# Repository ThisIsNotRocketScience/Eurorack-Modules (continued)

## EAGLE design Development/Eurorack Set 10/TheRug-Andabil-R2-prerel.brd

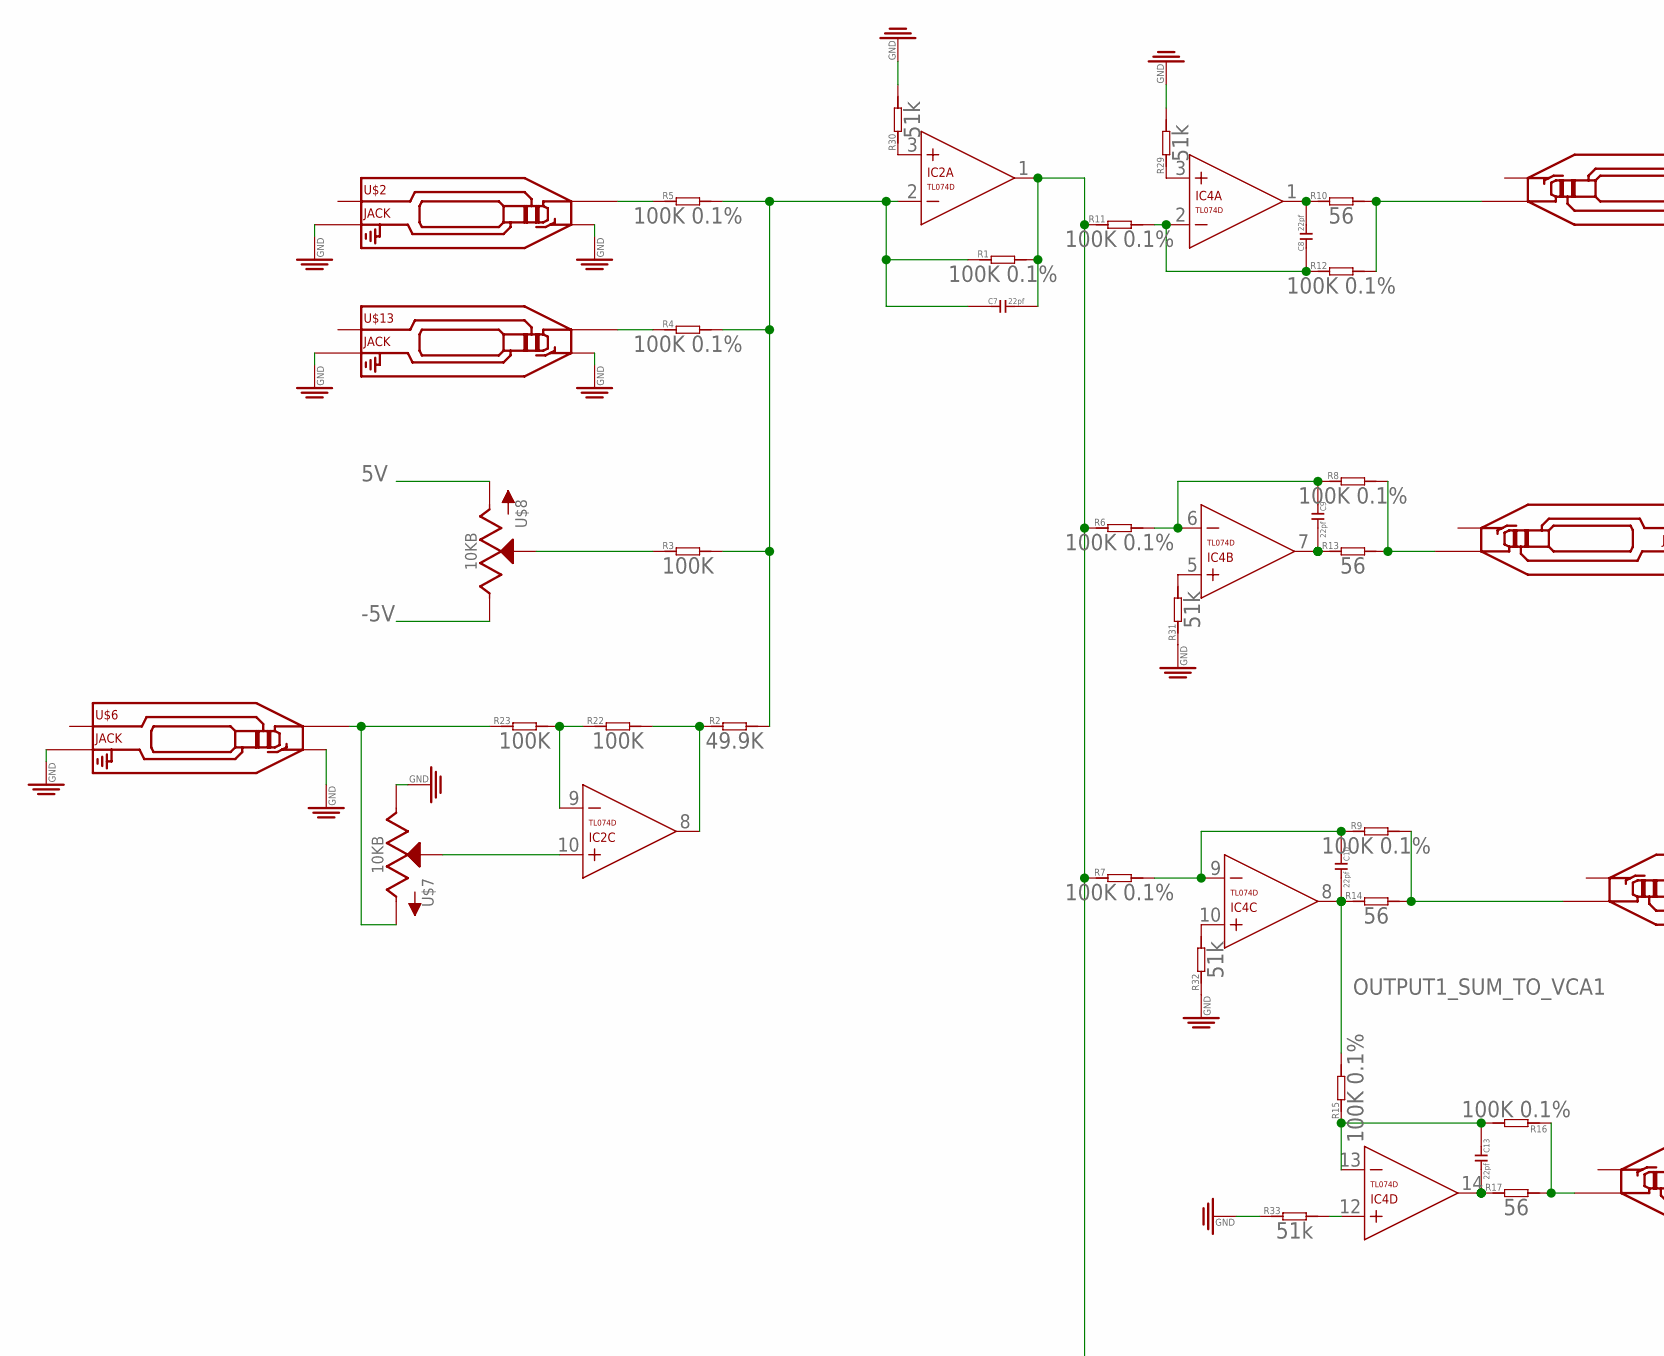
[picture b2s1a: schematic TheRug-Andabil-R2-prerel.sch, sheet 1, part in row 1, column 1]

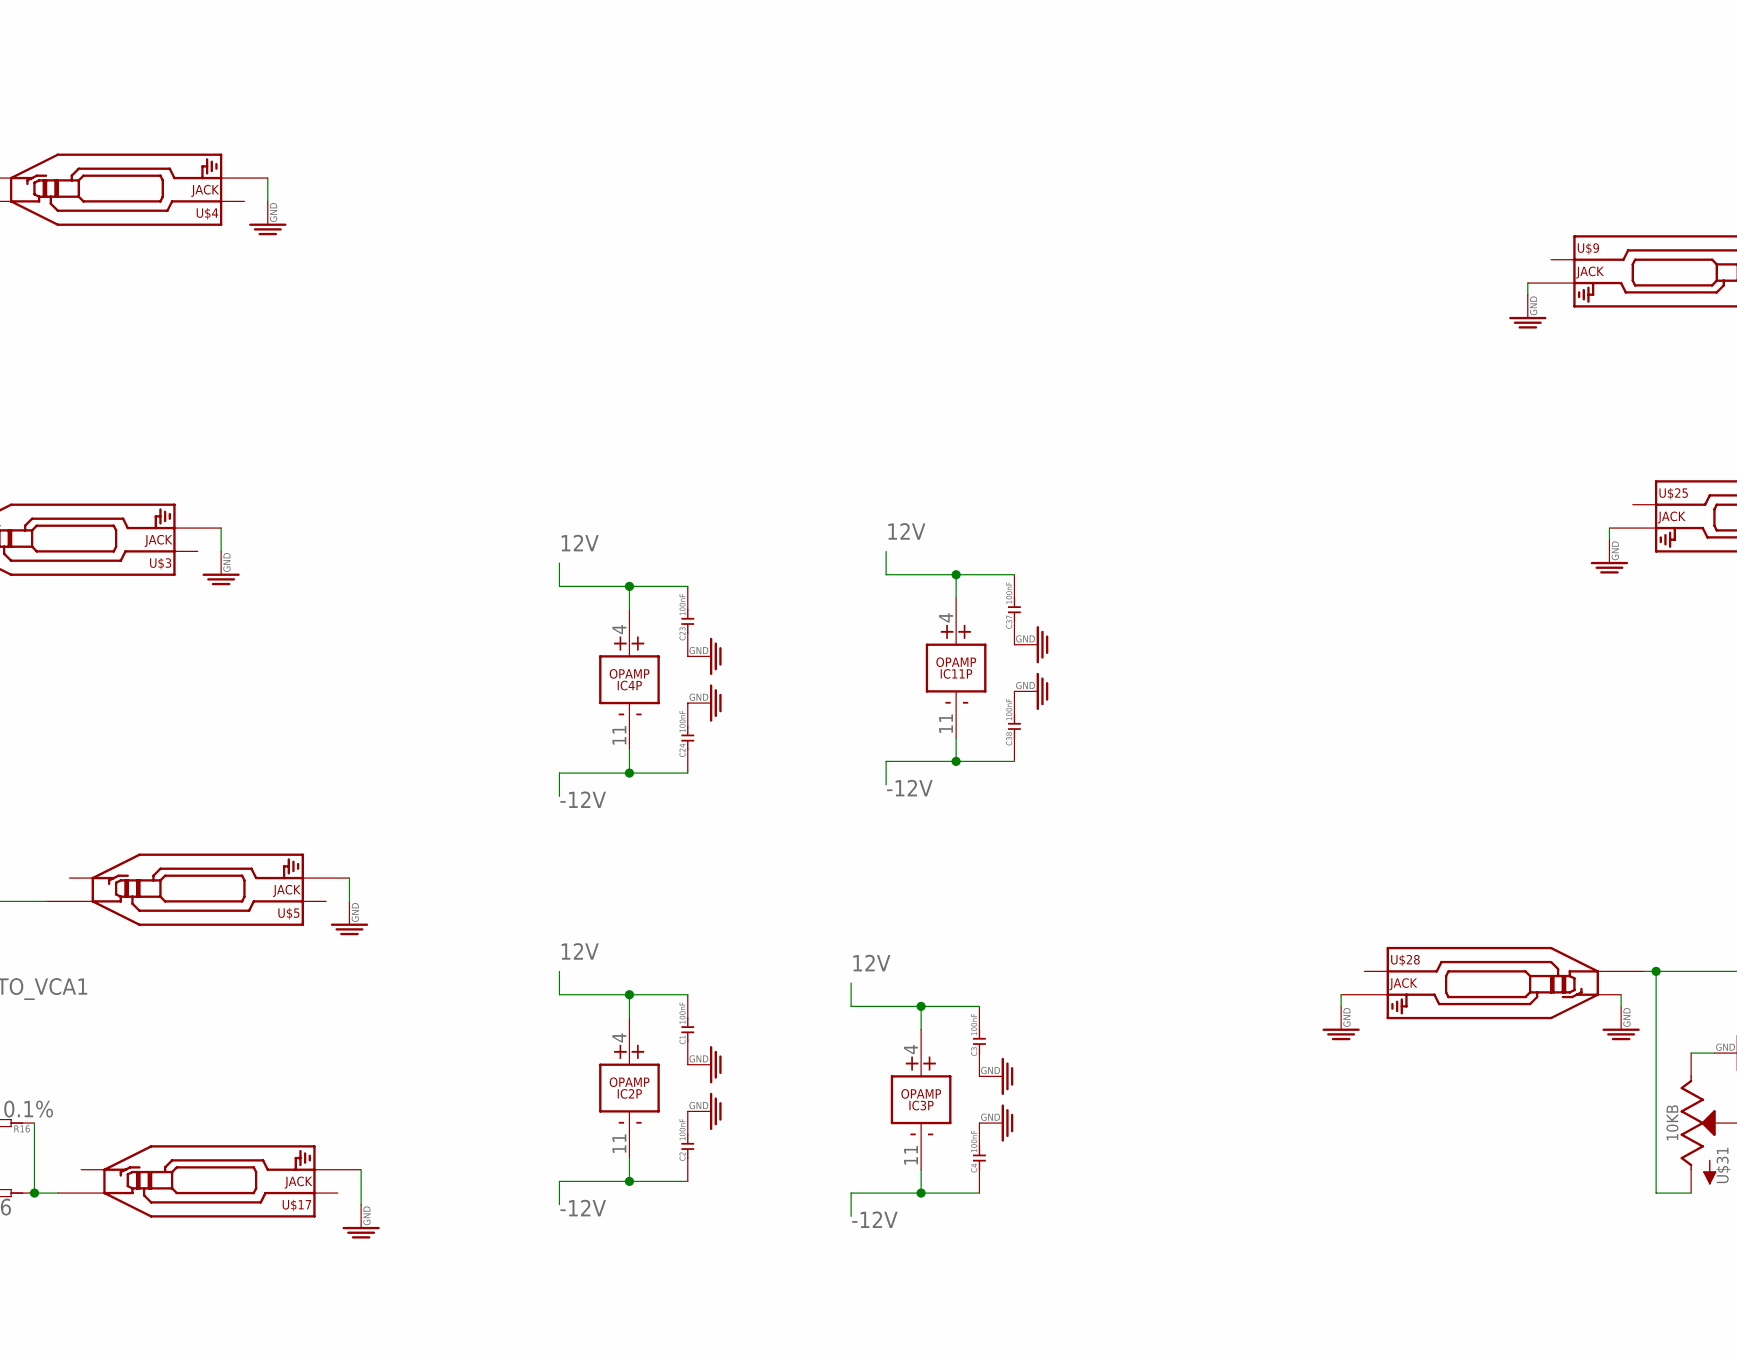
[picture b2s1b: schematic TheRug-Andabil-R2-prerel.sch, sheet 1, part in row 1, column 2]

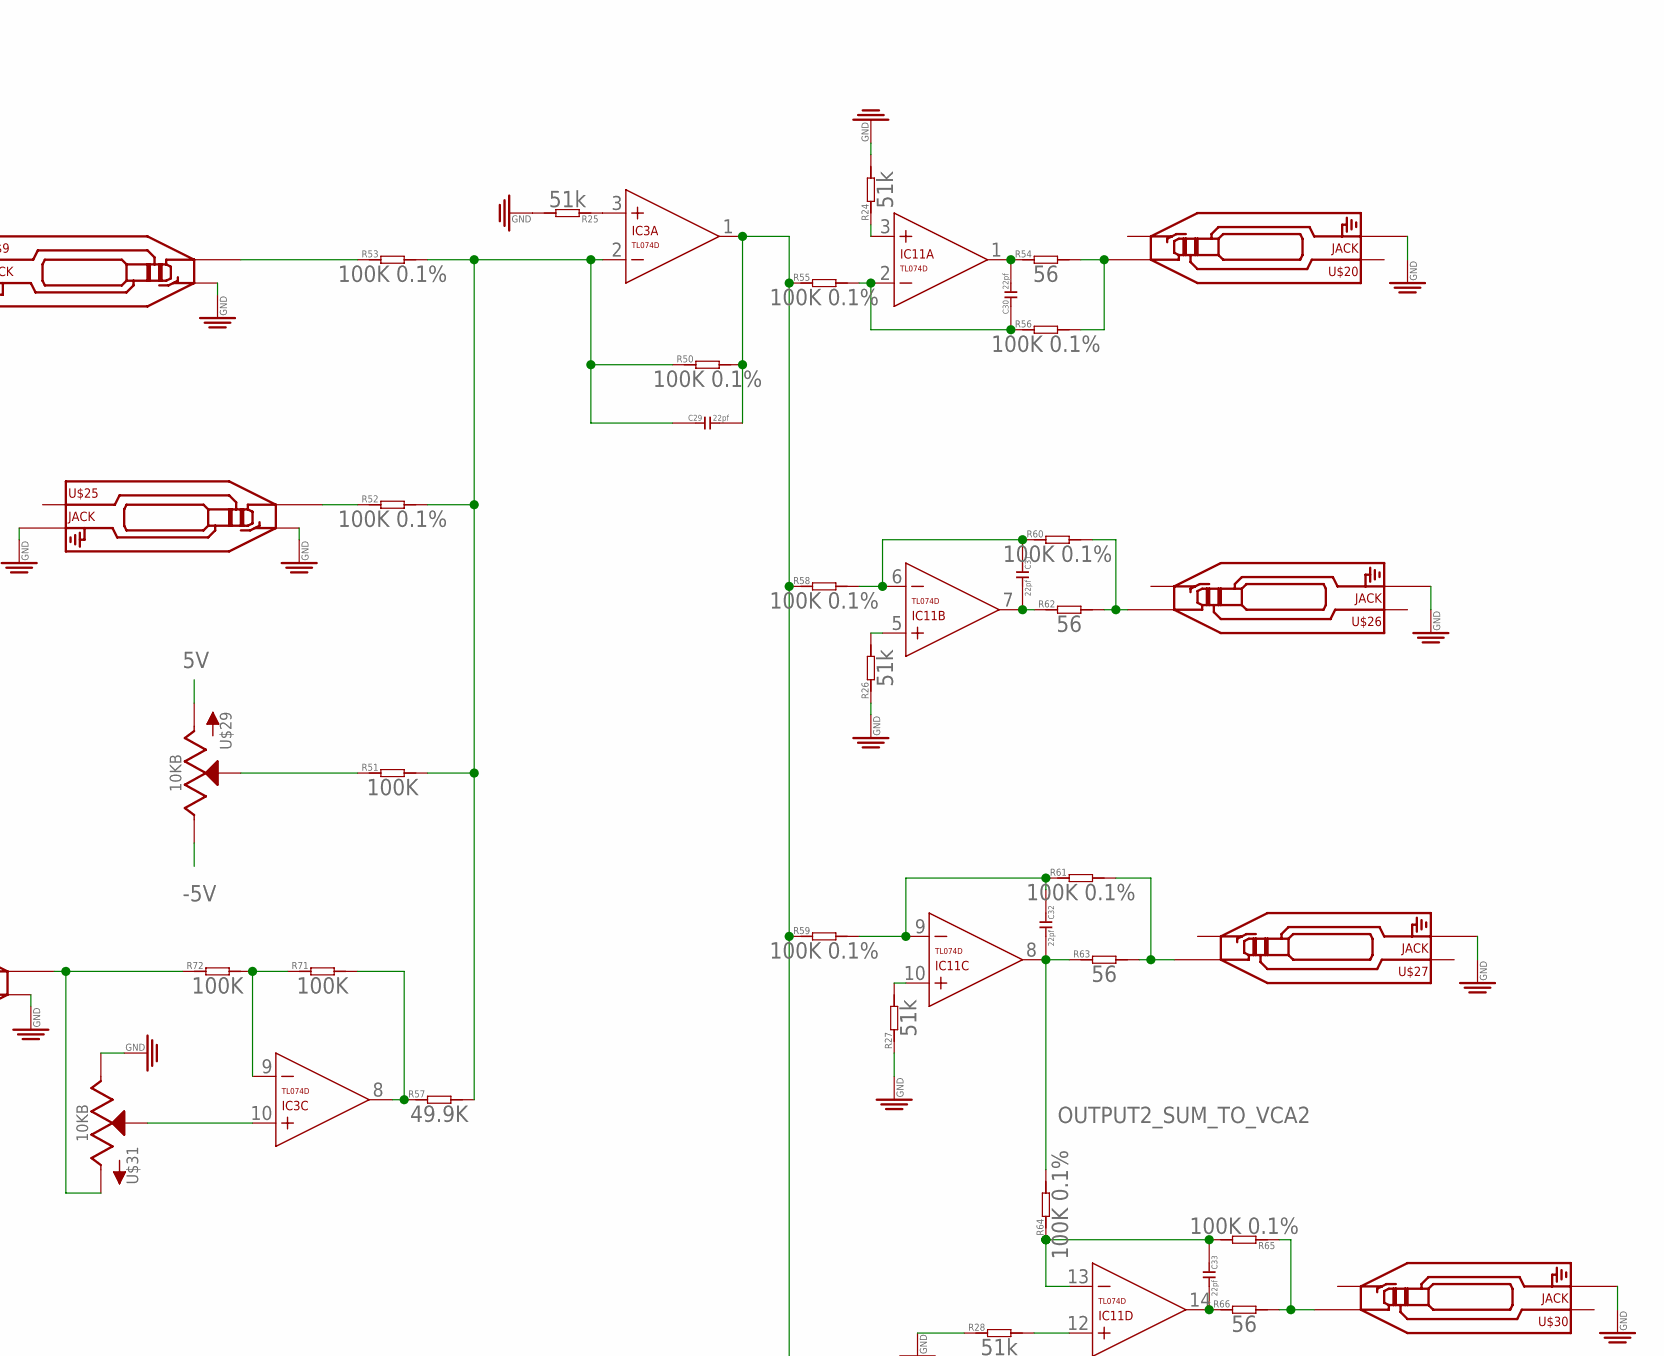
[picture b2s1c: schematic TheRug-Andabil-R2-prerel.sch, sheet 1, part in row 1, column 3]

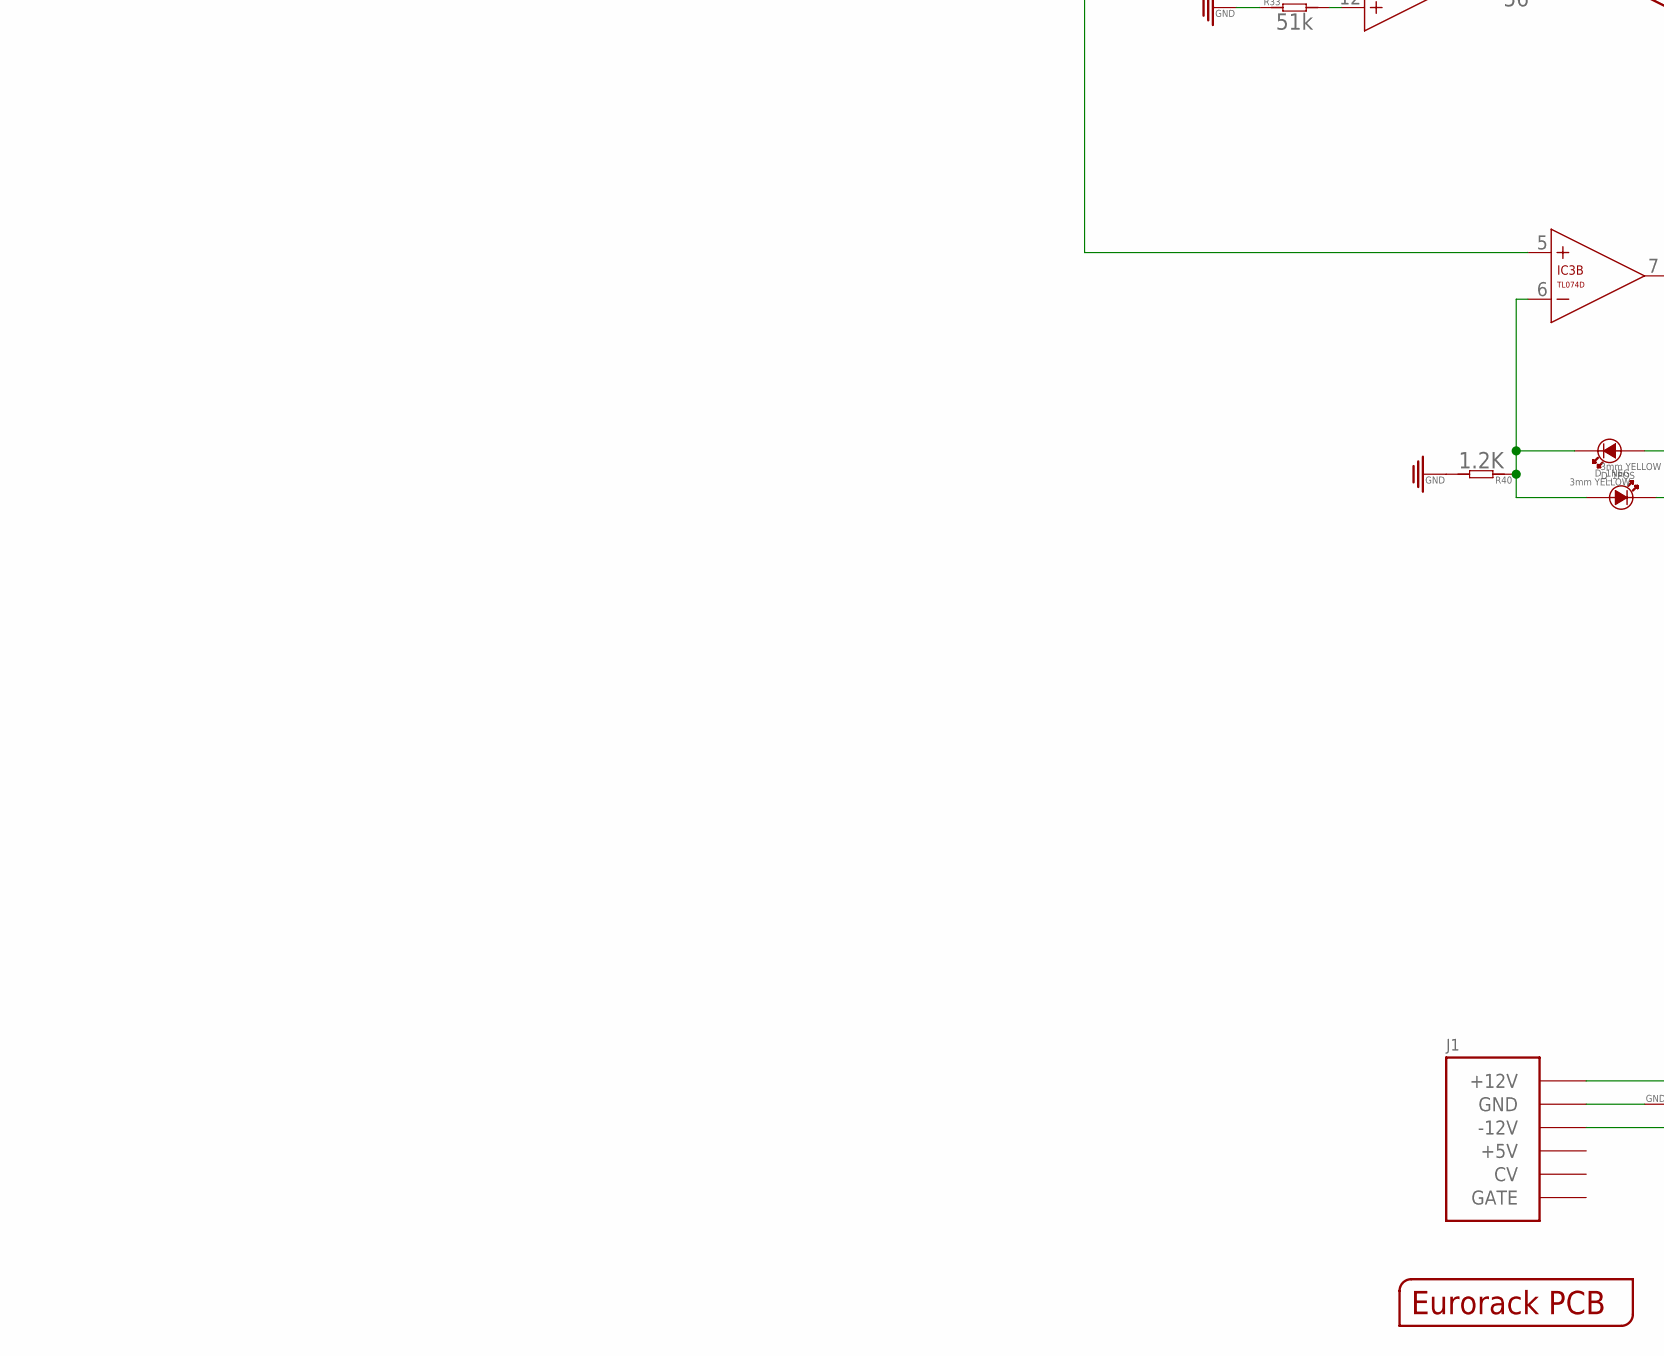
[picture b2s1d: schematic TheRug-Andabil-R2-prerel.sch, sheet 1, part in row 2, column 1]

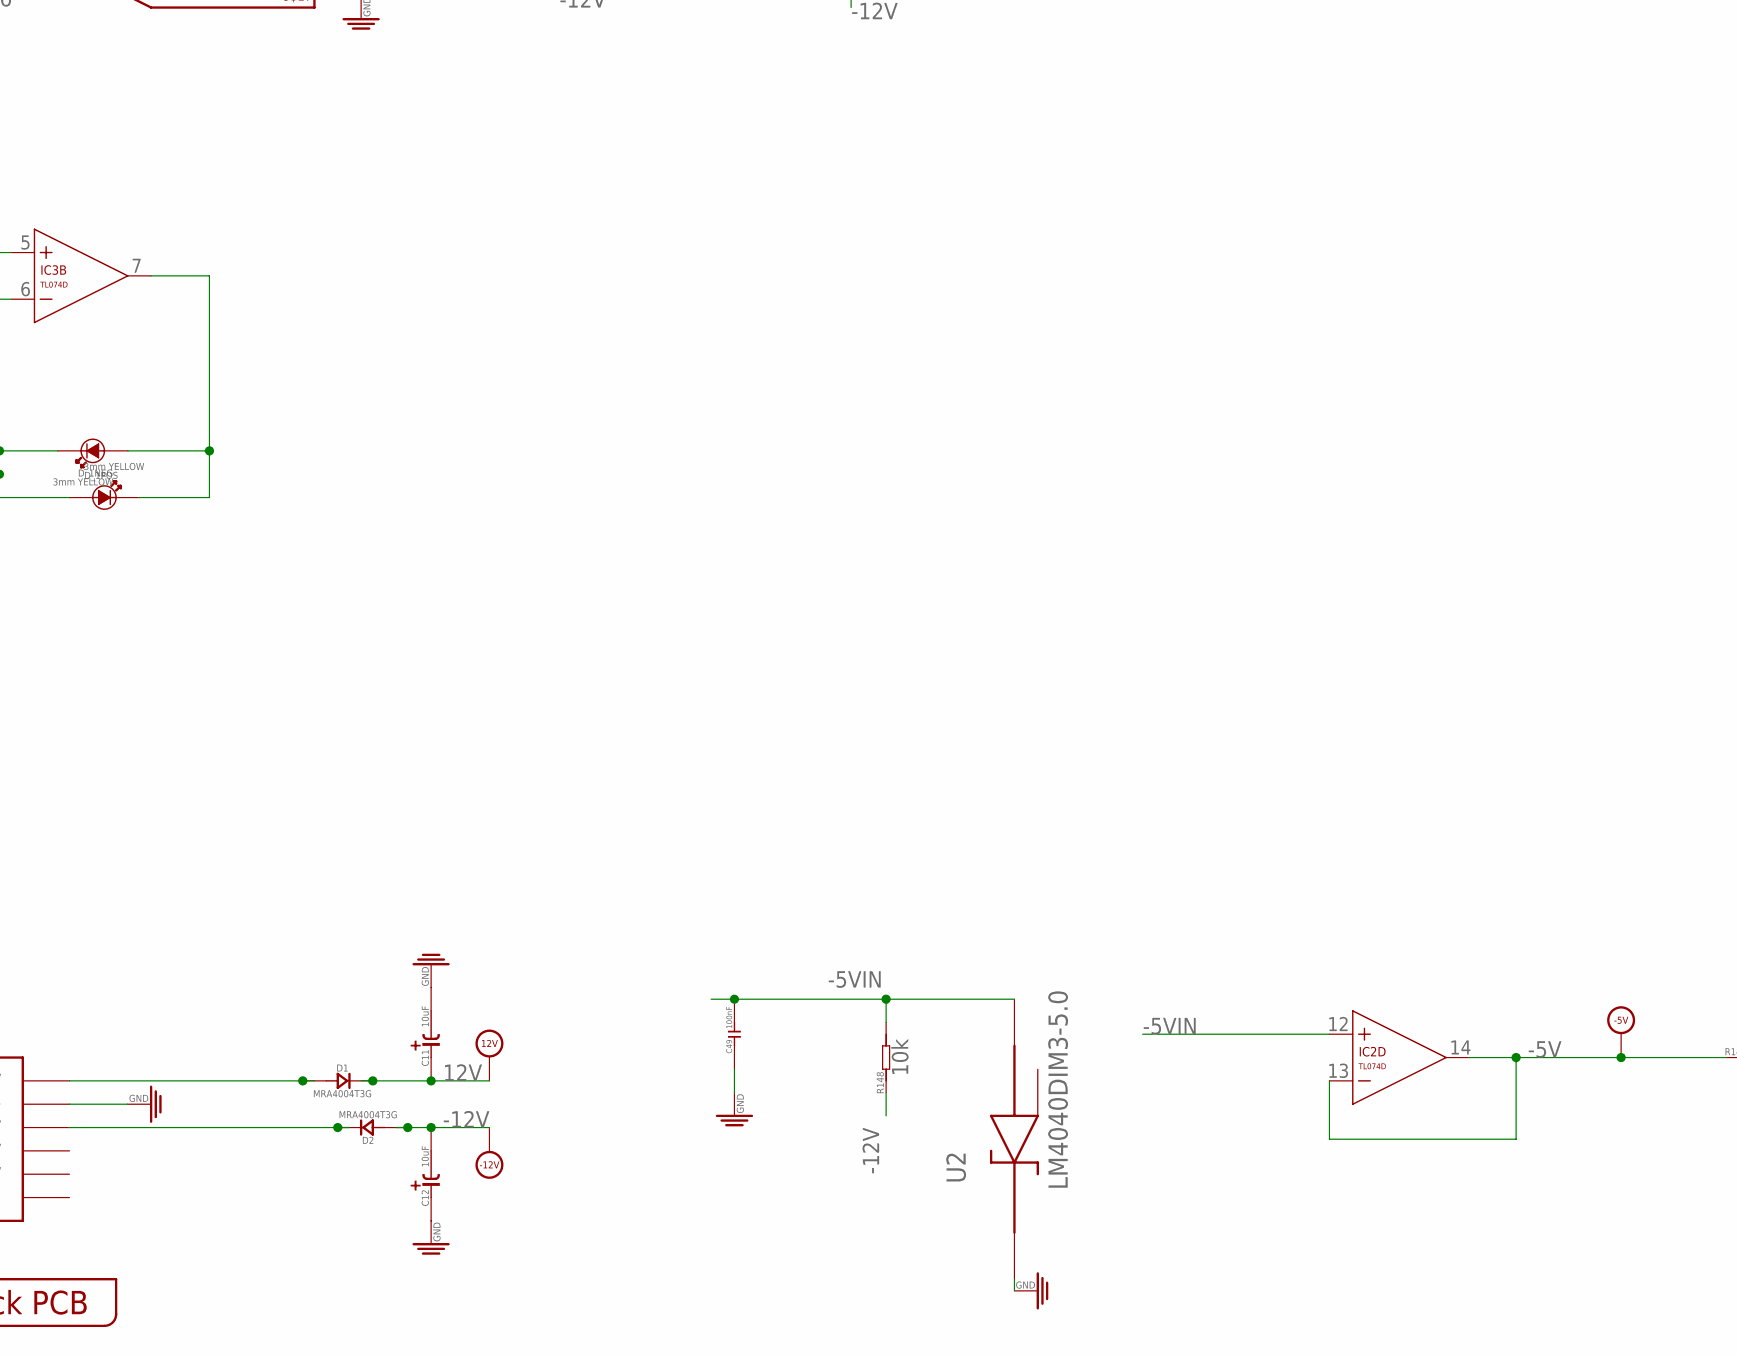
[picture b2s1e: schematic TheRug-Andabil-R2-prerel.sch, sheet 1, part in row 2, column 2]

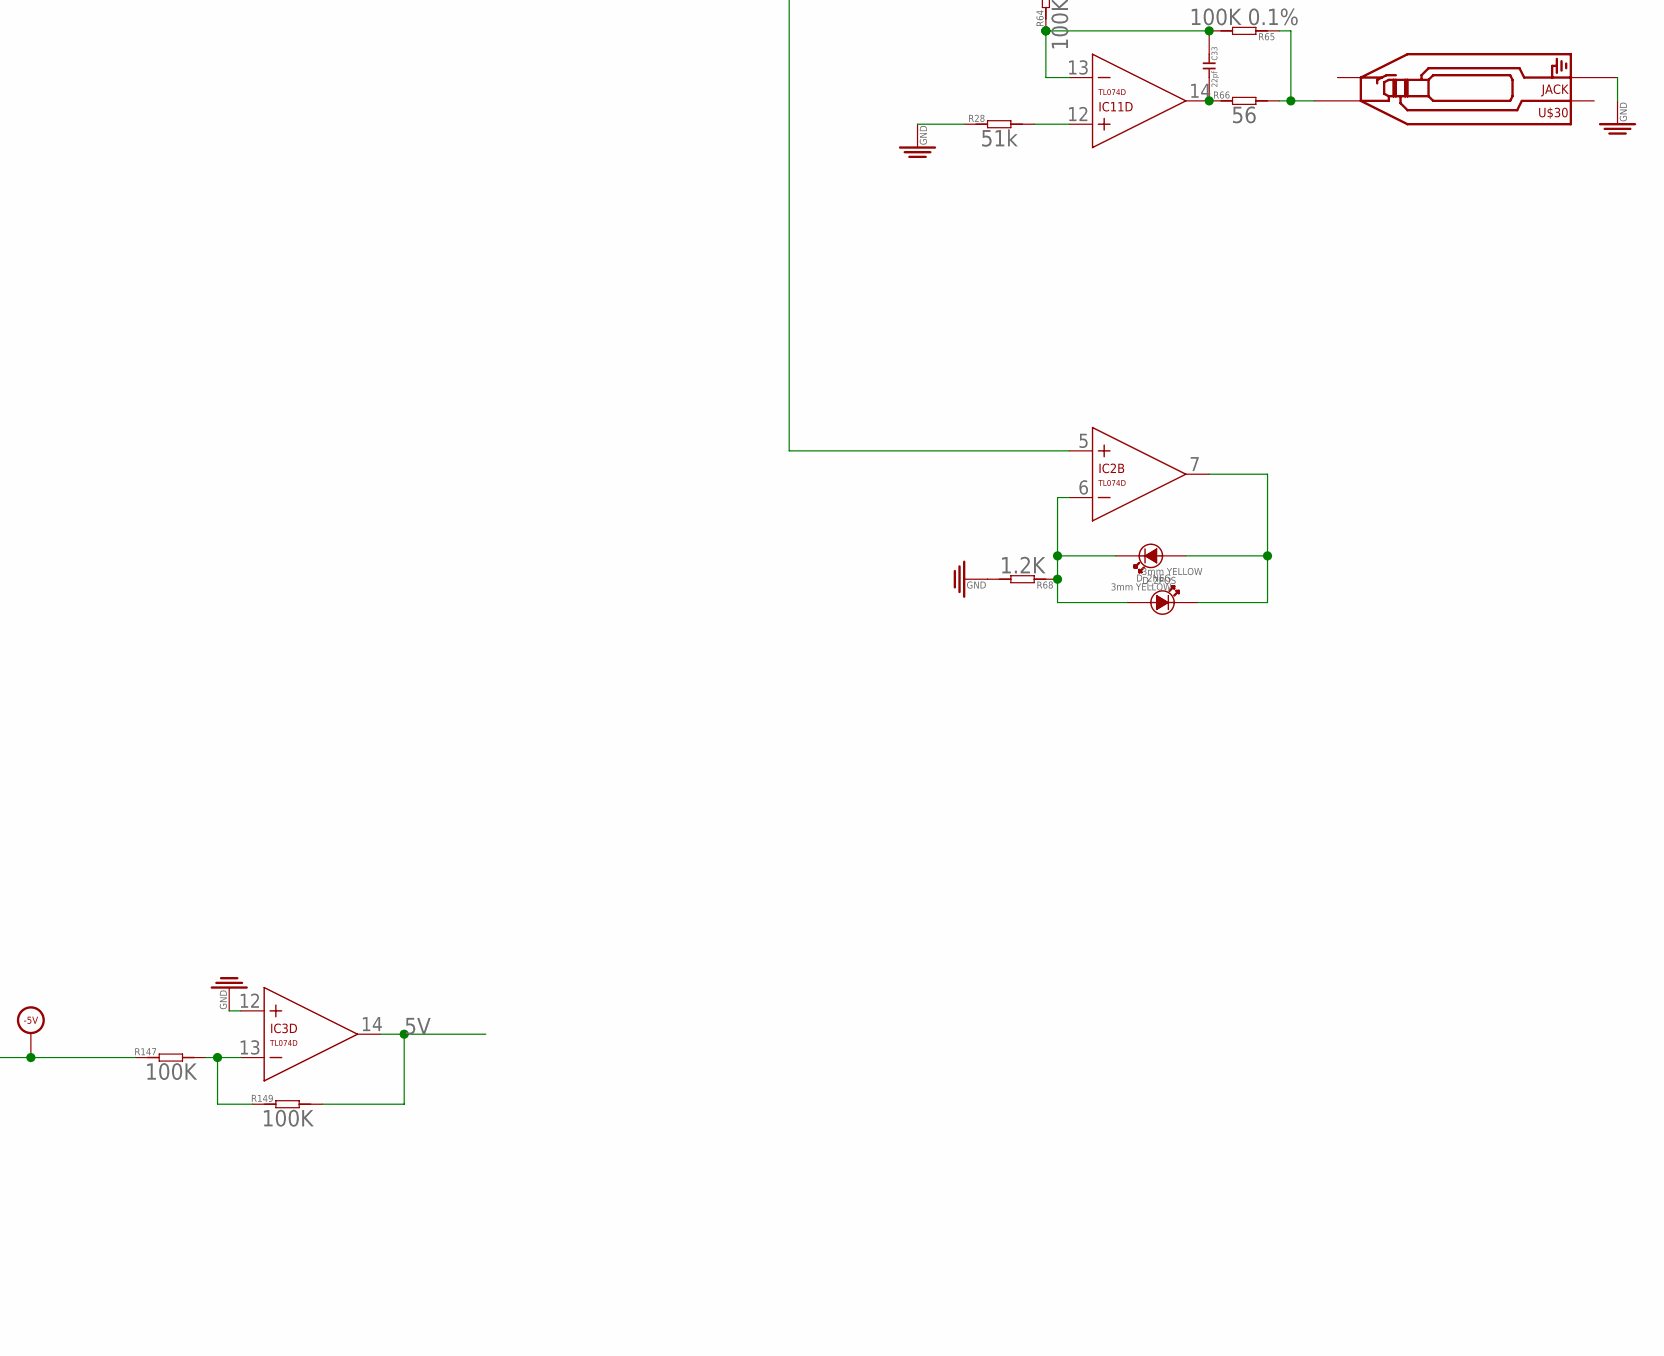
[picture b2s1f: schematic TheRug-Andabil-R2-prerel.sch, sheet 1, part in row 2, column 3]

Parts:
C1, C2, C3, C4, C23, C24, C37, C38: 100nF; C0603
C7, C8, C9, C10, C13, C29, C30, C31, C32, C33: 22pf; C0603
C11, C12: 10uF; CASE-A_3216
C49: 100nF; C0603; MPN 06035C104KAT2A
D1, D2: MRA4004T3G; DO-214AC; MPN US1G-E3/5AT
D_1NEG, D_1POS, D_2NEG, D_2POS: 3mm YELLOW; 3MMLED
IC2, IC3, IC4, IC11: TL074D; SO14
J1: POWERSHROUDED; POWER_16_SHROUDED
R1, R4, R5, R6, R7, R8, R9, R11, R12, R15, R16, R50, R52, R53, R55, R56, R58, R59, R60, R61, R64, R65: 100K 0.1%; R0603
R2, R57: 49.9K; R0603
R3, R22, R23, R51, R71, R72, R147, R149: 100K; R0603
R10, R13, R14, R17, R54, R62, R63, R66: 56; R0603
R24, R25, R26, R27, R28, R29, R30, R31, R32, R33: 51k; R0603
R40, R68: 1.2K; R0603
R148: 10k; R0603
U2: LM4040DIM3-5.0; SOT95P237X112-3N
U$1: EURORACK_PCB12HP; EURORACK12HPPCB
U$2, U$3, U$4, U$5, U$6, U$9, U$13, U$17, U$20, U$25, U$26, U$27, U$28, U$30: JACK; 3.5MM-JACK-SWITCH-13MM-NOHOLES
U$7, U$8, U$29, U$31: 10KB; ALPS_POT_SQUAREHOLES

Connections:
5V: IC3.14 (OUT), R149.2, U$8.P$3 (A), U$29.P$3 (A)
12V: C1.2, C3.2, C11.+ (1), C23.2, C37.2, D1.2 (-), IC2.4 (V+), IC3.4 (V+), IC4.4 (V+), IC11.4 (V+); also elsewhere on the board
-5V: IC2.13 (-IN), IC2.14 (OUT), R147.1, U$8.P$1 (E), U$29.P$1 (E); also elsewhere on the board
-5VIN: C49.2, IC2.12 (+IN), R148.2, U2.2 (ANODE)
-5V_TO_5V: IC3.13 (-IN), R147.2, R149.1
-12V: C2.1, C4.1, C12.- (2), C24.1, C38.1, D2.1 (+), IC2.11 (V-), IC3.11 (V-), IC4.11 (V-), IC11.11 (V-), R148.1; also elsewhere on the board
GND: C1.1, C2.2, C3.1, C4.2, C11.- (2), C12.+ (1), C23.1, C24.2, C37.1, C38.2, C49.1, IC3.12 (+IN), J1.3 (GND), J1.4 (GND), J1.5 (GND), J1.6 (GND), J1.7 (GND), J1.8 (GND), R24.2, R25.2, R26.1, R27.1, R28.1, R29.2, R30.2, R31.1, R32.1, R33.1, R40.2, R68.2, U2.1 (CATHODE), U$2.RING_B@1 (RING), U$2.RING_T@3 (RING), U$2.SWITCH_B@1 (SWITCH), U$2.SWITCH_T@3 (SWITCH), U$3.RING_B@1 (RING), U$3.RING_T@3 (RING), U$4.RING_B@1 (RING), U$4.RING_T@3 (RING), U$5.RING_B@1 (RING), U$5.RING_T@3 (RING), U$6.RING_B@1 (RING), U$6.RING_T@3 (RING), U$6.SWITCH_B@1 (SWITCH), U$6.SWITCH_T@3 (SWITCH), U$7.P$1 (E), U$9.RING_B@1 (RING), U$9.RING_T@3 (RING), U$9.SWITCH_B@1 (SWITCH), U$9.SWITCH_T@3 (SWITCH), U$13.RING_B@1 (RING), U$13.RING_T@3 (RING), U$13.SWITCH_B@1 (SWITCH), U$13.SWITCH_T@3 (SWITCH), U$17.RING_B@1 (RING), U$17.RING_T@3 (RING), U$20.RING_B@1 (RING), U$20.RING_T@3 (RING), U$25.RING_B@1 (RING), U$25.RING_T@3 (RING), U$25.SWITCH_B@1 (SWITCH), U$25.SWITCH_T@3 (SWITCH), U$26.RING_B@1 (RING), U$26.RING_T@3 (RING), U$27.RING_B@1 (RING), U$27.RING_T@3 (RING), U$28.RING_B@1 (RING), U$28.RING_T@3 (RING), U$28.SWITCH_B@1 (SWITCH), U$28.SWITCH_T@3 (SWITCH), U$30.RING_B@1 (RING), U$30.RING_T@3 (RING), U$31.P$1 (E); also elsewhere on the board
unnamed: IC2.10 (+IN), U$7.P$2 (S)
unnamed: C8.2, IC4.1 (OUT), R10.1
unnamed: IC2.8 (OUT), R2.1, R22.2
unnamed: R23.1, U$6.TIP_B@1 (TIP), U$6.TIP_T@3 (TIP), U$7.P$3 (A)
unnamed: C9.1, IC4.6 (-IN), R6.2, R8.1
unnamed: R3.1, U$8.P$2 (S)
unnamed: C7.2, IC2.1 (OUT), IC3.5 (+IN), R1.2, R6.1, R7.1, R11.1
unnamed: C8.1, IC4.2 (-IN), R11.2, R12.1
unnamed: C10.1, IC4.9 (-IN), R7.2, R9.1
unnamed: IC2.9 (-IN), R22.1, R23.2
unnamed: C9.2, IC4.7 (OUT), R13.1
unnamed: R4.1, U$13.TIP_B@1 (TIP), U$13.TIP_T@3 (TIP)
unnamed: R60.2, R62.2, U$26.TIP_B@1 (TIP), U$26.TIP_T@3 (TIP)
unnamed: C7.1, IC2.2 (-IN), R1.1, R2.2, R3.2, R4.2, R5.2
unnamed: R8.2, R13.2, U$3.TIP_B@1 (TIP), U$3.TIP_T@3 (TIP)
unnamed: R9.2, R14.2, U$5.TIP_B@1 (TIP), U$5.TIP_T@3 (TIP)
unnamed: C13.1, IC4.13 (-IN), R15.1, R16.2
unnamed: C13.2, IC4.14 (OUT), R17.1
unnamed: R16.1, R17.2, U$17.TIP_B@1 (TIP), U$17.TIP_T@3 (TIP)
unnamed: R5.1, U$2.TIP_B@1 (TIP), U$2.TIP_T@3 (TIP)
unnamed: R10.2, R12.2, U$4.TIP_B@1 (TIP), U$4.TIP_T@3 (TIP)
unnamed: IC11.3 (+IN), R24.1
unnamed: IC3.3 (+IN), R25.1
unnamed: D1.1 (+), J1.9 (+12V), J1.10 (+12V)
unnamed: IC11.5 (+IN), R26.2
unnamed: IC11.10 (+IN), R27.2
unnamed: R65.1, R66.2, U$30.TIP_B@1 (TIP), U$30.TIP_T@3 (TIP)
unnamed: IC11.12 (+IN), R28.2
unnamed: IC4.3 (+IN), R29.1
unnamed: IC2.3 (+IN), R30.1
unnamed: IC4.5 (+IN), R31.2
unnamed: IC4.10 (+IN), R32.2
unnamed: IC4.12 (+IN), R33.2
unnamed: D_1NEG.-, D_1POS.+, IC3.6 (-IN), R40.1
unnamed: D_1NEG.+, D_1POS.-, IC3.7 (OUT)
unnamed: C30.2, IC11.1 (OUT), R54.1
unnamed: R51.1, U$29.P$2 (S)
unnamed: R52.1, U$25.TIP_B@1 (TIP), U$25.TIP_T@3 (TIP)
unnamed: D2.2 (-), J1.1 (-12V), J1.2 (-12V)
unnamed: C29.1, IC3.2 (-IN), R50.1, R51.2, R52.2, R53.2, R57.2
unnamed: R54.2, R56.2, U$20.TIP_B@1 (TIP), U$20.TIP_T@3 (TIP)
unnamed: C29.2, IC2.5 (+IN), IC3.1 (OUT), R50.2, R55.1, R58.1, R59.1
unnamed: C30.1, IC11.2 (-IN), R55.2, R56.1
unnamed: R53.1, U$9.TIP_B@1 (TIP), U$9.TIP_T@3 (TIP)
unnamed: R72.1, U$28.TIP_B@1 (TIP), U$28.TIP_T@3 (TIP), U$31.P$3 (A)
unnamed: C31.1, IC11.6 (-IN), R58.2, R60.1
unnamed: C32.1, IC11.9 (-IN), R59.2, R61.1
unnamed: C31.2, IC11.7 (OUT), R62.1
unnamed: R61.2, R63.2, U$27.TIP_B@1 (TIP), U$27.TIP_T@3 (TIP)
unnamed: C33.1, IC11.13 (-IN), R64.1, R65.2
unnamed: C33.2, IC11.14 (OUT), R66.1
unnamed: D_2NEG.-, D_2POS.+, IC2.6 (-IN), R68.1
unnamed: D_2NEG.+, D_2POS.-, IC2.7 (OUT)
unnamed: IC3.10 (+IN), U$31.P$2 (S)
unnamed: IC3.8 (OUT), R57.1, R71.2
unnamed: IC3.9 (-IN), R71.1, R72.2
OUTPUT1_SUM_TO_VCA1: C10.2, IC4.8 (OUT), R14.1, R15.2; also elsewhere on the board
OUTPUT2_SUM_TO_VCA2: C32.2, IC11.8 (OUT), R63.1, R64.2; also elsewhere on the board
